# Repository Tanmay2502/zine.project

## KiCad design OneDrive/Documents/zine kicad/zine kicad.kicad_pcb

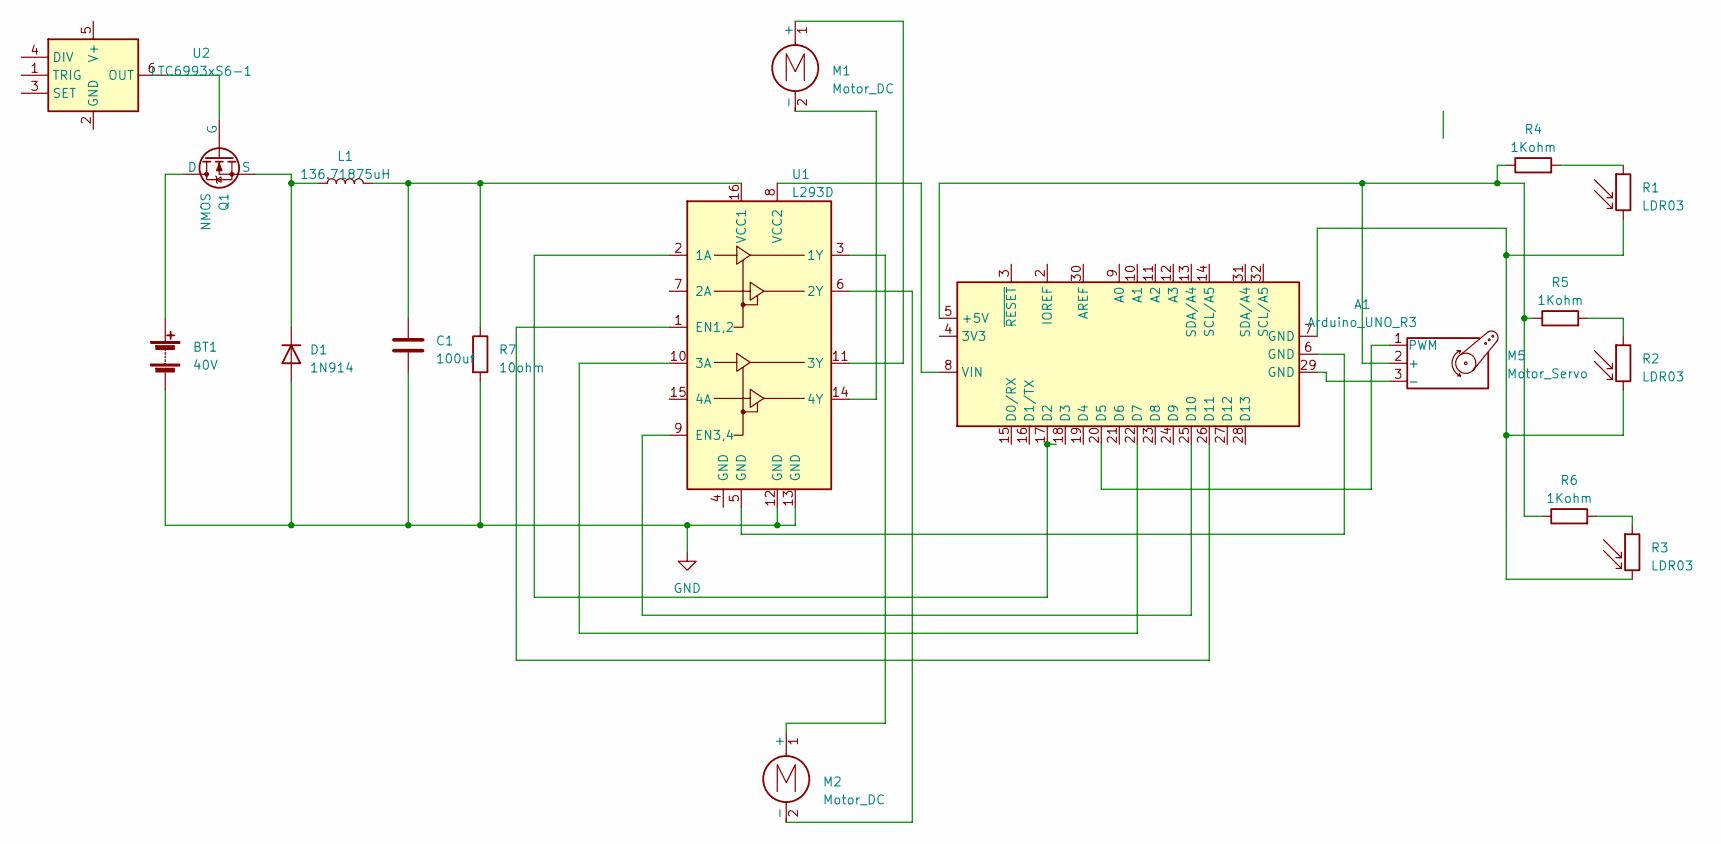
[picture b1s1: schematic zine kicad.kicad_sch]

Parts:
A1: Arduino_UNO_R3
BT1: 40V; BatteryHolder_Eagle_12BH611-GR
C1: 100uf; CP_Elec_3x5.4
D1: 1N914; D_DO-35_SOD27_P7.62mm_Horizontal
L1: 136.71875uH; L_Wuerth_HCI-2212
M1, M2: Motor_DC; Vybronics_VZ30C1T8219732L
M5: Motor_Servo; Vybronics_VZ30C1T8219732L
Q1: NMOS; TO-220-3_Vertical
R1, R2, R3: LDR03; R_LDR_10x8.5mm_P7.6mm_Vertical
R4, R5, R6: 1Kohm; R_0402_1005Metric
R7: 10ohm; R_0402_1005Metric
U1: L293D; DIP-16_W7.62mm
U2: LTC6993xS6-1; TSOT-23-6

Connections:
GND: BT1.2 (-), C1.2, D1.2 (A), R7.2, U1.12 (GND), U1.13 (GND)
unnamed: A1.5 (+5V), M5.2 (+), R4.1, R5.1, R6.1
unnamed: A1.17 (D2), U1.2 (1A)
unnamed: A1.20 (D5), M5.1 (PWM)
unnamed: A1.22 (D7), U1.10 (3A)
unnamed: A1.25 (D10), U1.9 (EN3,4)
unnamed: A1.26 (D11), U1.1 (EN1,2)
unnamed: A1.6 (GND), U1.5 (GND)
unnamed: A1.7 (GND), R1.2, R2.2, R3.2
unnamed: A1.8 (VIN), U1.8 (VCC2)
unnamed: BT1.1 (+), Q1.1 (D)
unnamed: D1.1 (K), L1.1, Q1.3 (S)
unnamed: M1.1 (+), U1.11 (3Y)
unnamed: M1.2 (-), U1.14 (4Y)
unnamed: M2.1 (+), U1.3 (1Y)
unnamed: M2.2 (-), U1.6 (2Y)
unnamed: A1.29 (GND), M5.3 (-)
unnamed: Q1.2 (G), U2.6 (OUT)
unnamed: R1.1, R4.2
unnamed: R2.1, R5.2
unnamed: R3.1, R6.2
unnamed: C1.1, L1.2, R7.1, U1.16 (VCC1)

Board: 2 copper layers, 18 parts (0 on the bottom side), 21 nets, no tracks yet.

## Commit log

2023-04-18 link for tinkercad
2023-04-19 diagram for bot
2023-04-21 Buck Converter Diagram
2023-04-22 Kicad Diagram
2023-05-02 OneDrive/Documents/zine.project.md
2023-05-10 OneDrive/Documents/zine kicad
